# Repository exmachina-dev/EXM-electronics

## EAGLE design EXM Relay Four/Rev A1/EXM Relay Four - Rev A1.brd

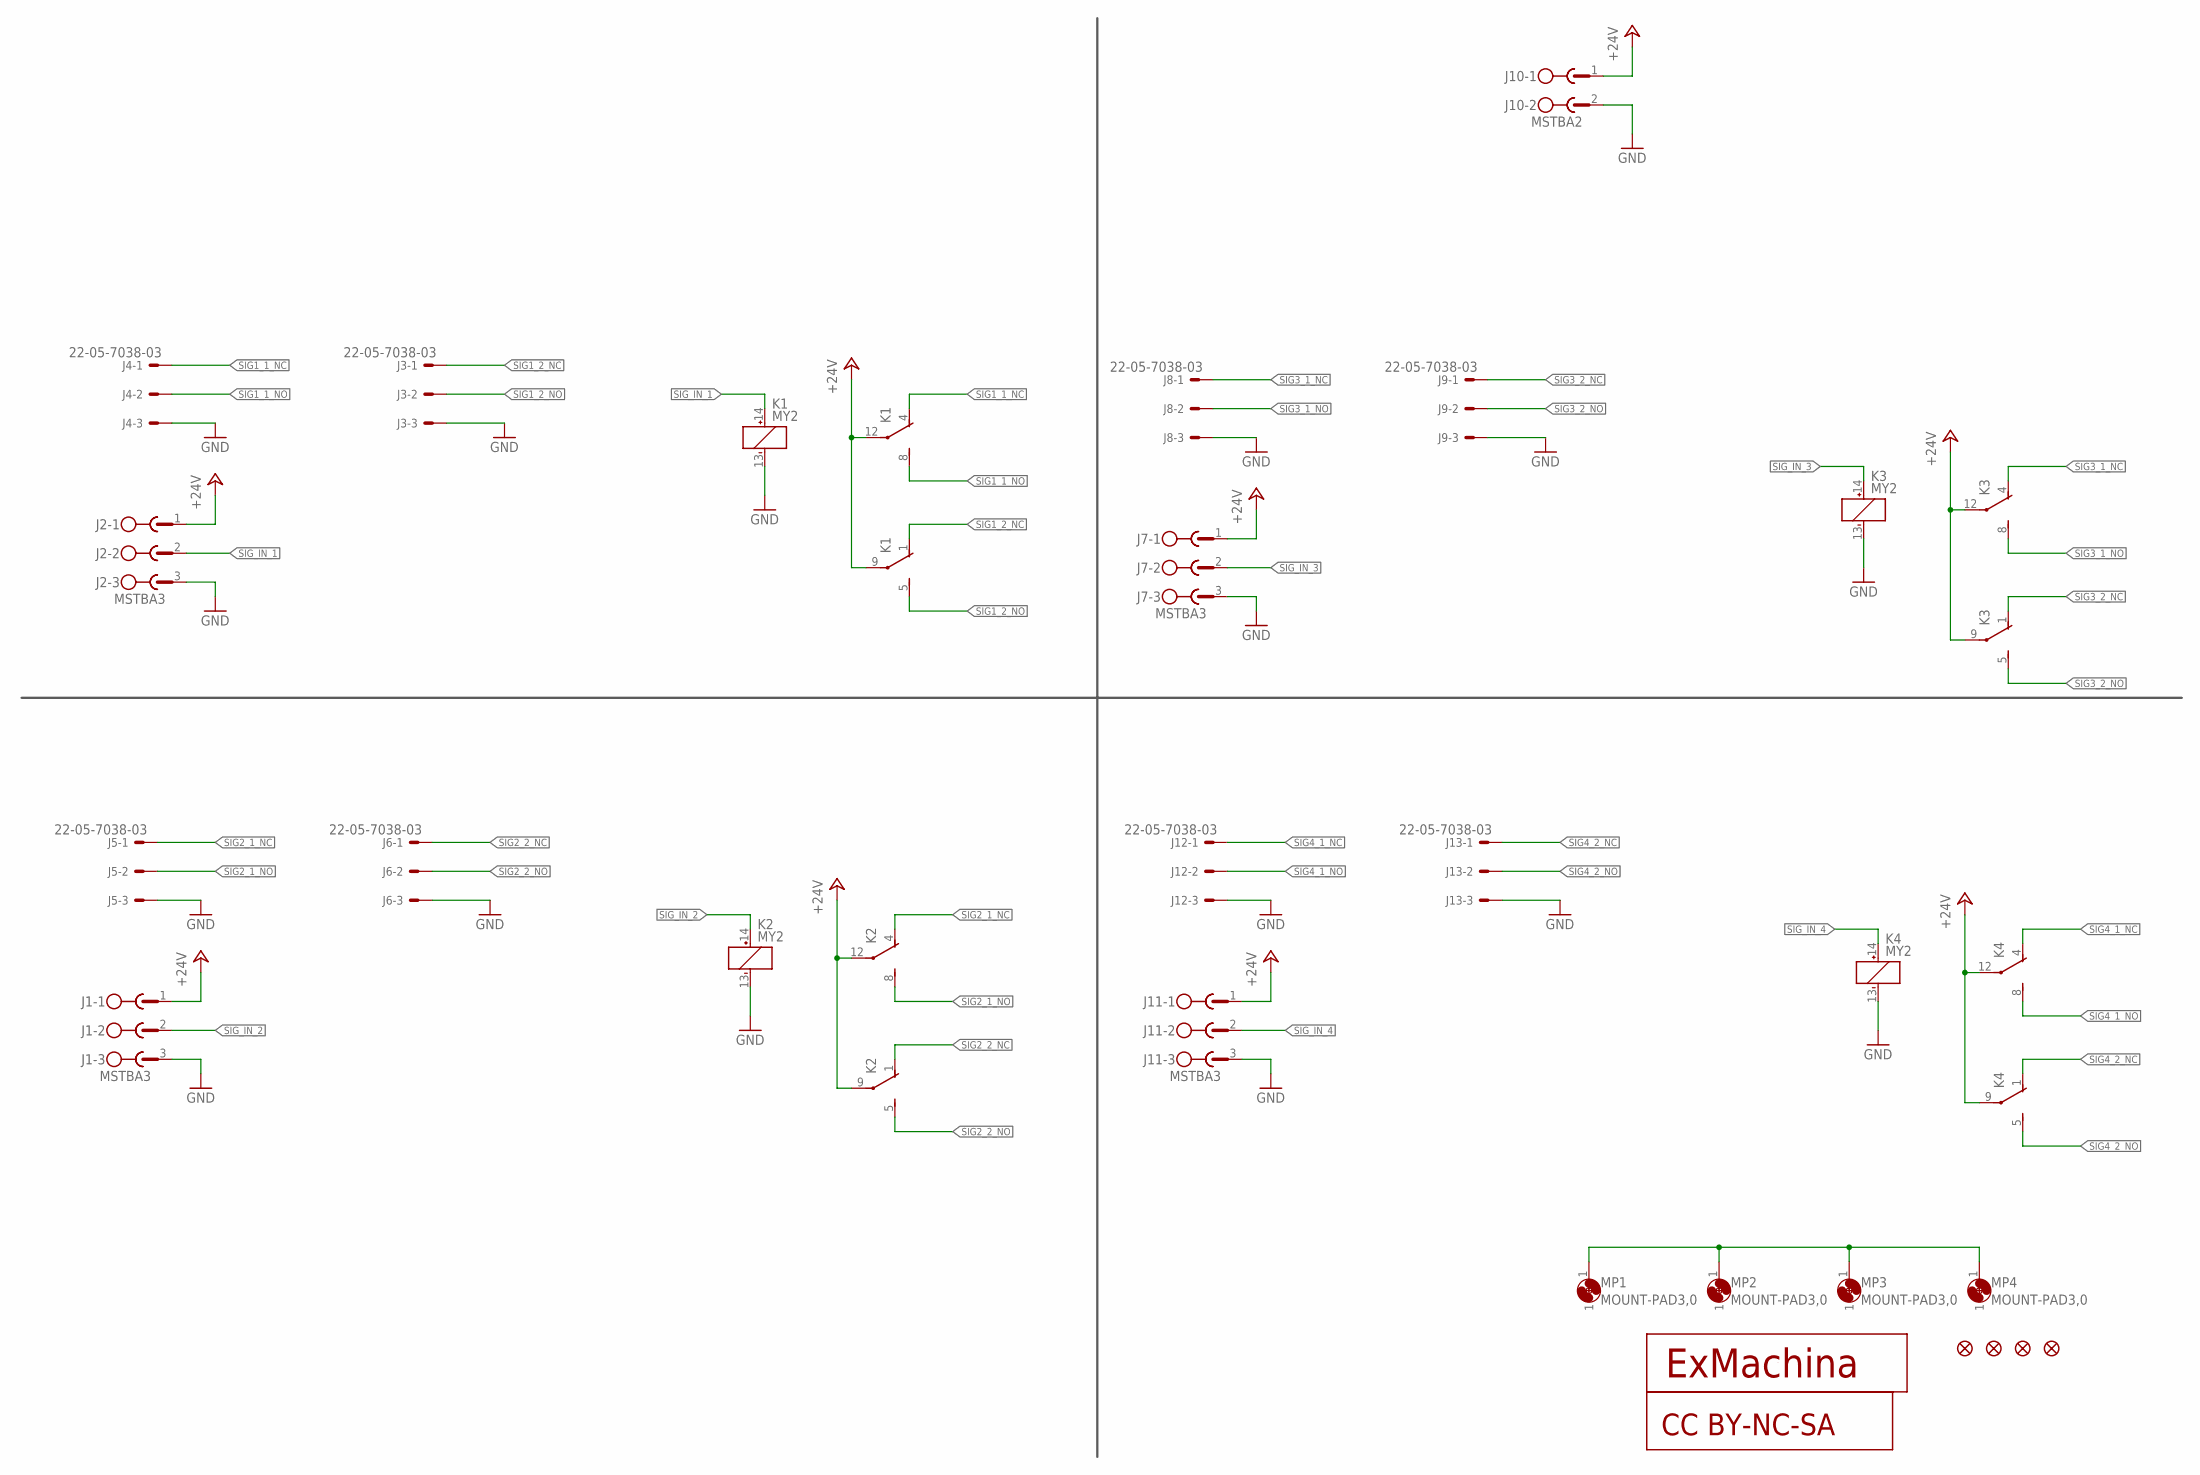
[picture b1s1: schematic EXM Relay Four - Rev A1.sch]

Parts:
CC1: CC-BY-NC-SA
J1, J2, J7, J11: MSTBA3
J3, J4, J5, J6, J8, J9, J12, J13: 22-05-7038-03; 7395-03
J10: MSTBA2
JP1, JP2, JP3, JP4: FIDUCIAL1X2; FIDUCIAL-1X2
K1, K2, K3, K4: MY2; PY08
MP1, MP2, MP3, MP4: MOUNT-PAD3,0; P3,0
T1: EXMACHINA-LOGO-NAME; EXM-LOGO-BASELINE

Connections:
1: MP1.1, MP2.1, MP3.1, MP4.1
+24V: J1.1, J2.1, J7.1, J10.1, J11.1, K1.9 (C), K1.12 (C), K2.9 (C), K2.12 (C), K3.9 (C), K3.12 (C), K4.9 (C), K4.12 (C)
GND: J1.3, J2.3, J3.3, J4.3, J5.3, J6.3, J7.3, J8.3, J9.3, J10.2, J11.3, J12.3, J13.3, K1.13 (-), K2.13 (-), K3.13 (-), K4.13 (-)
SIG1_1_NC: J4.1, K1.4 (NC)
SIG1_1_NO: J4.2, K1.8 (NO)
SIG1_2_NC: J3.1, K1.1 (NC)
SIG1_2_NO: J3.2, K1.5 (NO)
SIG2_1_NC: J5.1, K2.4 (NC)
SIG2_1_NO: J5.2, K2.8 (NO)
SIG2_2_NC: J6.1, K2.1 (NC)
SIG2_2_NO: J6.2, K2.5 (NO)
SIG3_1_NC: J8.1, K3.4 (NC)
SIG3_1_NO: J8.2, K3.8 (NO)
SIG3_2_NC: J9.1, K3.1 (NC)
SIG3_2_NO: J9.2, K3.5 (NO)
SIG4_1_NC: J12.1, K4.4 (NC)
SIG4_1_NO: J12.2, K4.8 (NO)
SIG4_2_NC: J13.1, K4.1 (NC)
SIG4_2_NO: J13.2, K4.5 (NO)
SIG_IN_1: J2.2, K1.14 (+)
SIG_IN_2: J1.2, K2.14 (+)
SIG_IN_3: J7.2, K3.14 (+)
SIG_IN_4: J11.2, K4.14 (+)

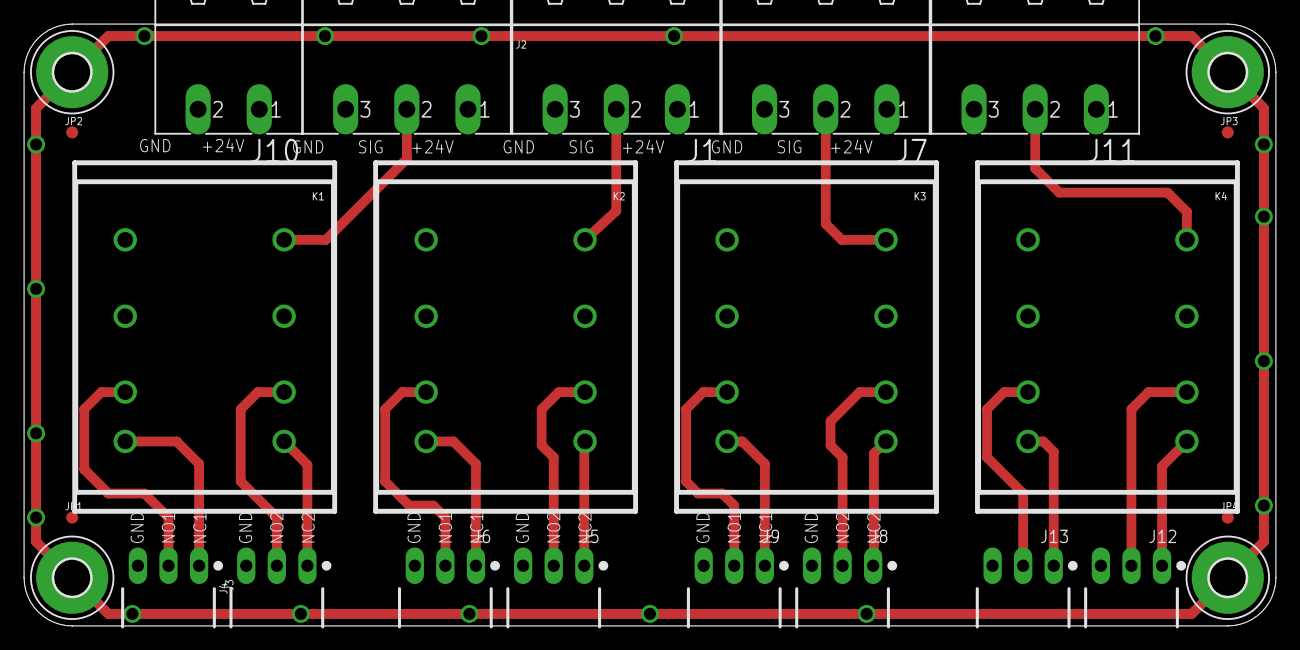
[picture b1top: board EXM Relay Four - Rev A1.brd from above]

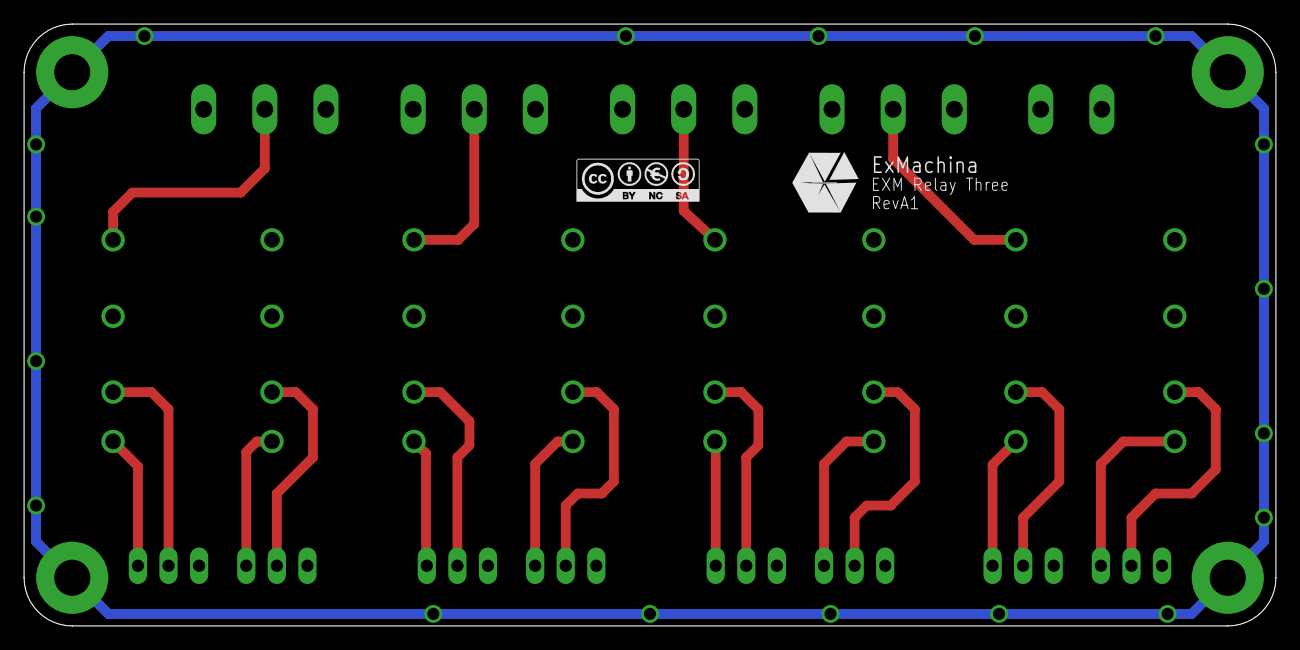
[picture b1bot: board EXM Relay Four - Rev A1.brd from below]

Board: 2 copper layers, 104.0 x 50.0 mm, 28 parts (2 on the bottom side), 23 nets.

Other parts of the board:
U$1: A4L-LOC

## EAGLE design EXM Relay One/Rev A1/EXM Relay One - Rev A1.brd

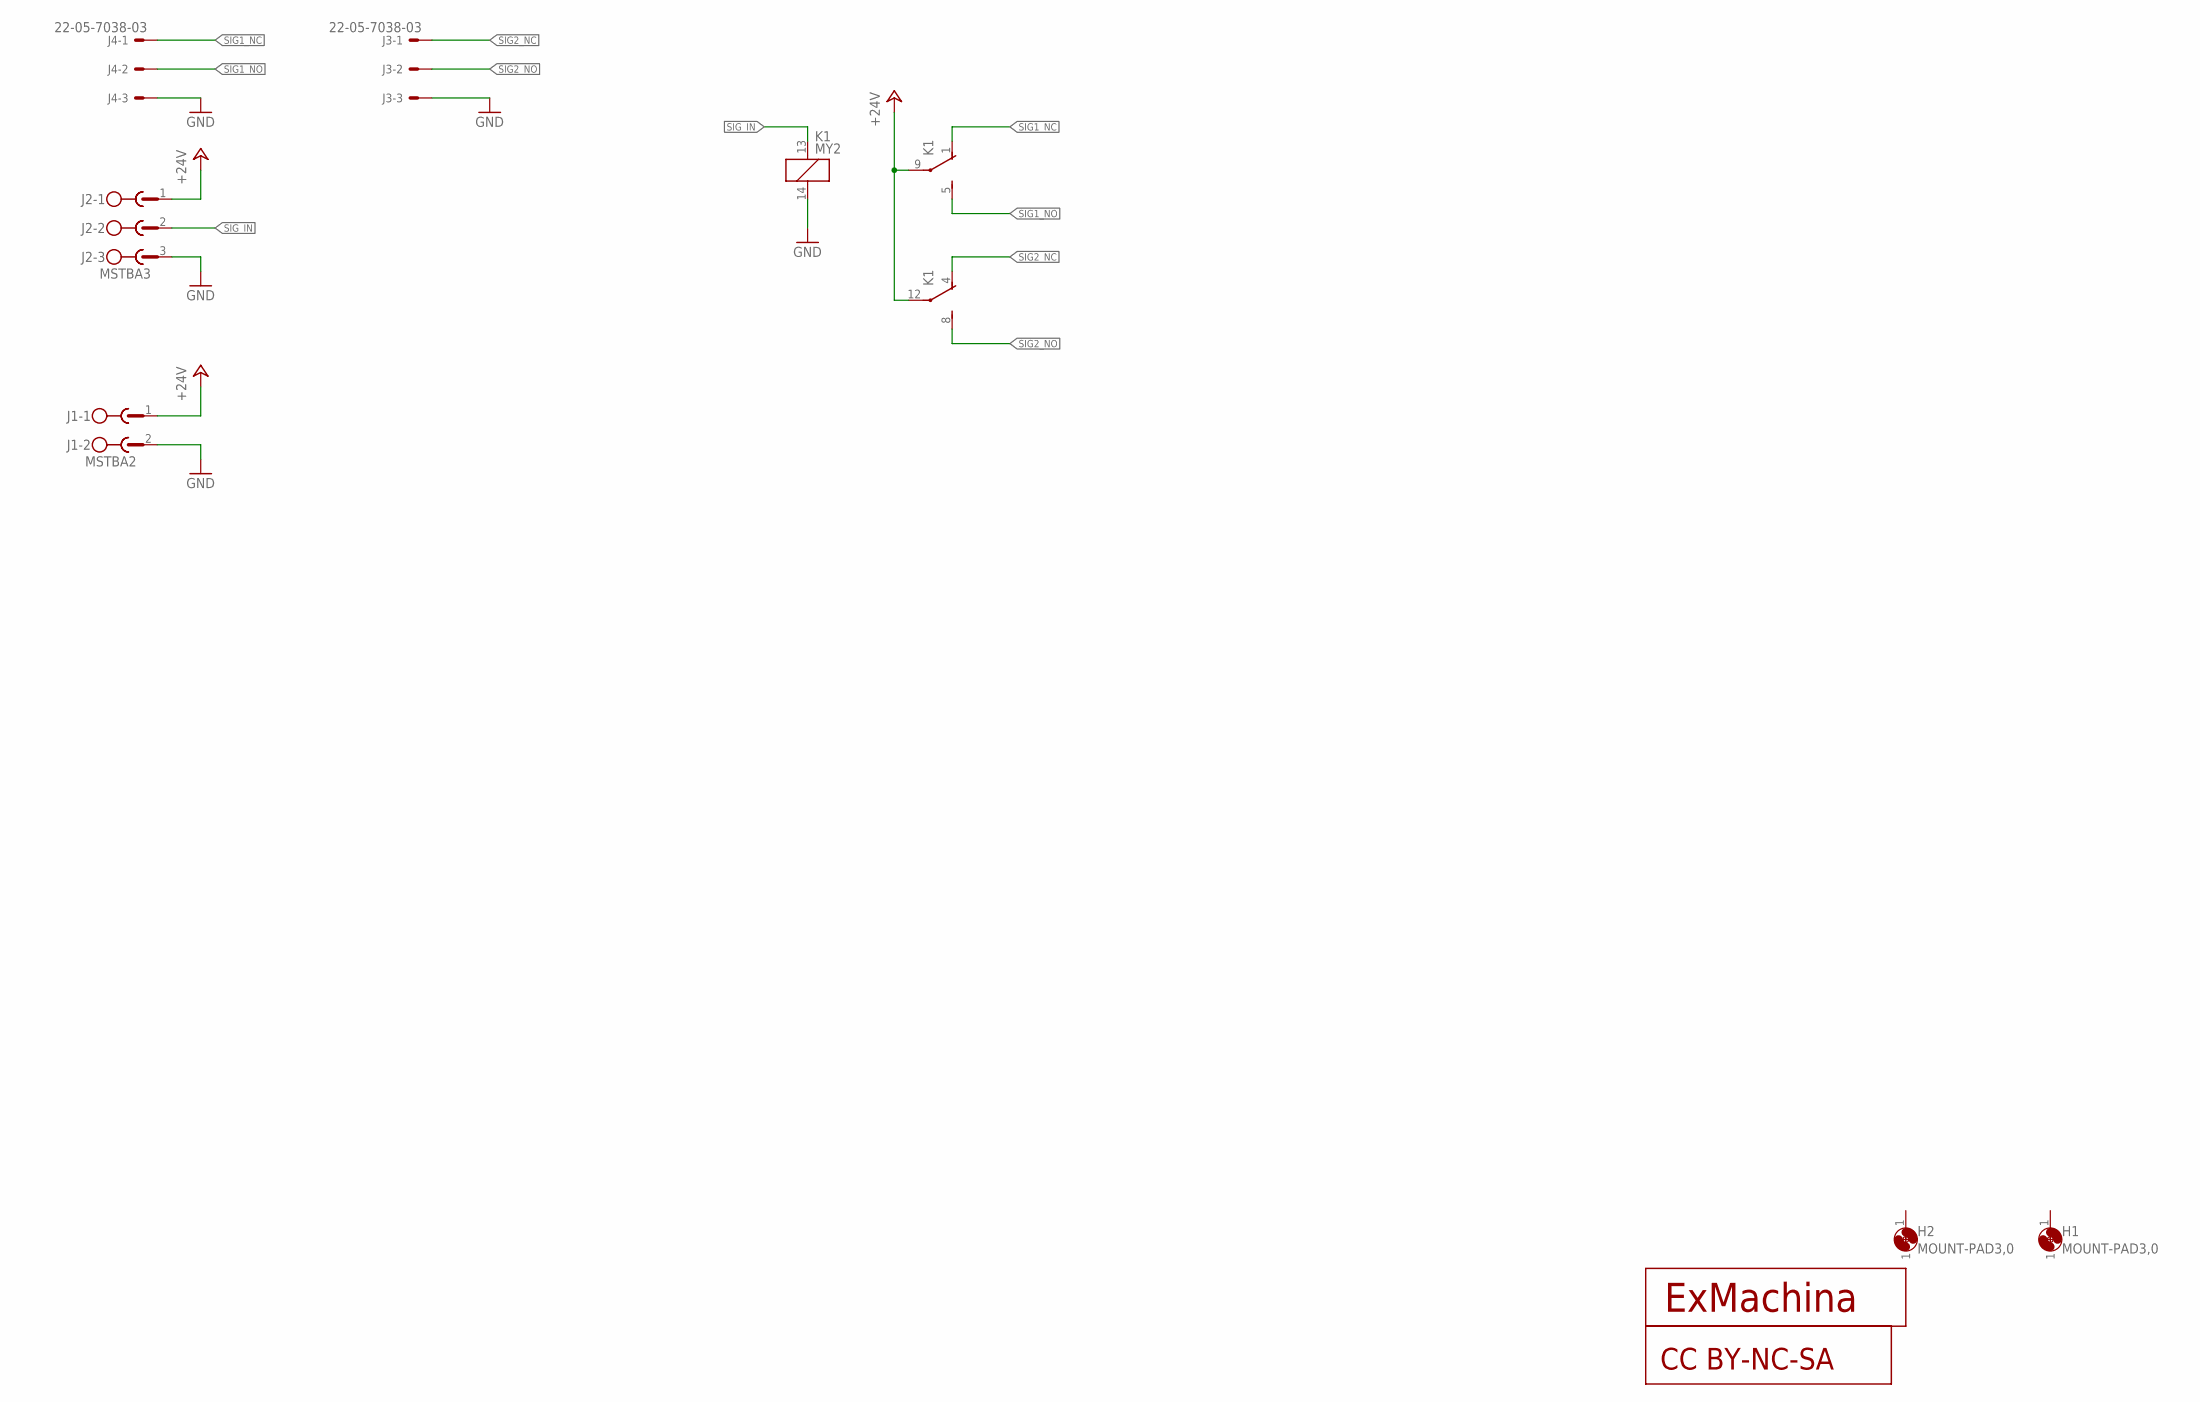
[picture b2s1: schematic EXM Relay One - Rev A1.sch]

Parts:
CC1: CC-BY-NC-SA
H1, H2: MOUNT-PAD3,0; P3,0
J1: MSTBA2
J2: MSTBA3
J3, J4: 22-05-7038-03; 7395-03
K1: MY2; PY08
T1: EXMACHINA-LOGO-NAME; EXM-LOGO-BASELINE

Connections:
+24V: J1.1, J2.1, K1.9 (C), K1.12 (C)
GND: J1.2, J2.3, J3.3, J4.3, K1.14 (COIL2)
SIG1_NC: J4.1, K1.1 (NO)
SIG1_NO: J4.2, K1.5 (NC)
SIG2_NC: J3.1, K1.4 (NO)
SIG2_NO: J3.2, K1.8 (NC)
SIG_IN: J2.2, K1.13 (COIL1)

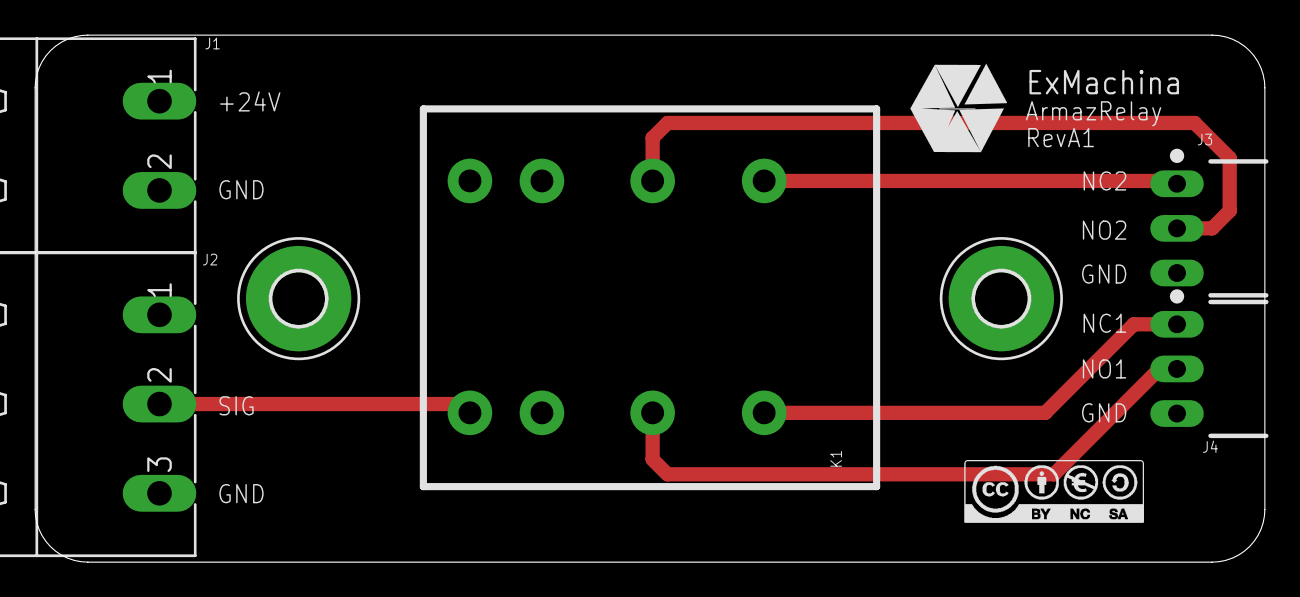
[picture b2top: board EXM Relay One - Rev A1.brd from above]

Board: 2 copper layers, 70.0 x 30.0 mm, 10 parts (0 on the bottom side), 7 nets.

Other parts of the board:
U$1: A4L-LOC

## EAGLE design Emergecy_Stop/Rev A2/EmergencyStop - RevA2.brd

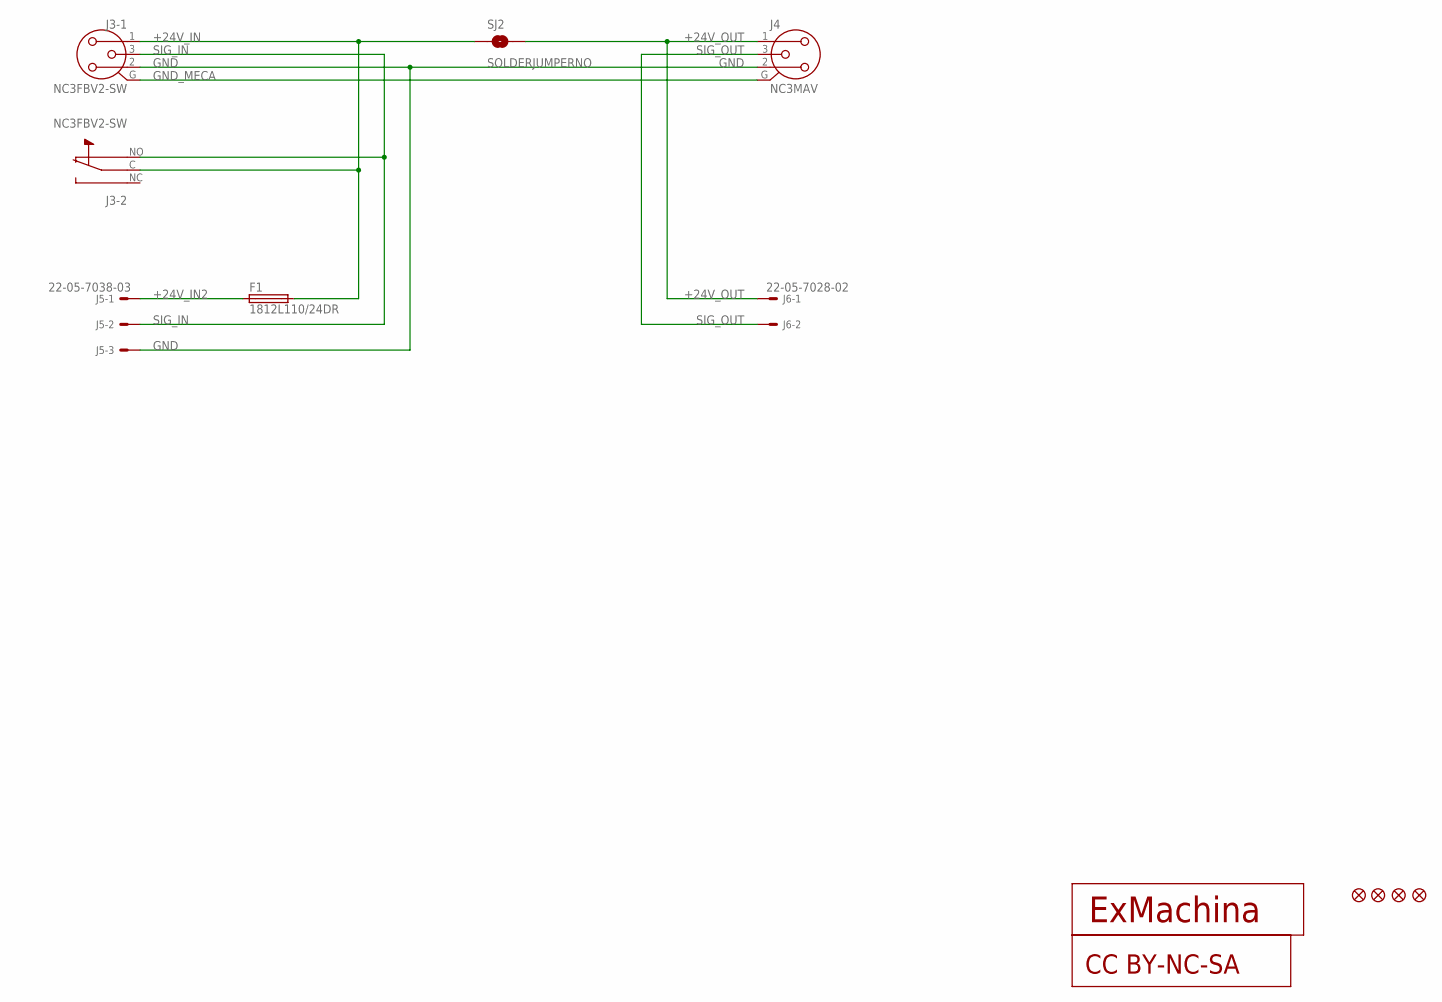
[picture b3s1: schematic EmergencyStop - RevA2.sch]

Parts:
CC1: CC-BY-NC-SA
F1: 1812L110/24DR; LITTLEFUSE_SMD
J3: NC3FBV2-SW
J4: NC3MAV
J5: 22-05-7038-03; 7395-03
J6: 22-05-7028-02; 7395-02
JP1, JP2, JP3, JP4: FIDUCIAL1X2; FIDUCIAL-1X2
SJ2: SOLDERJUMPERNO; SJ_2S-NO
T1: EXMACHINA-LOGO-NAME; EXM-LOGO-BASELINE

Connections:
+24V_IN: F1.2, J3.1, J3.C (N), SJ2.1
+24V_IN2: F1.1, J5.1
+24V_OUT: J4.1, J6.1, SJ2.2
GND: J3.2, J4.2, J5.3
GND_MECA: J3.G, J4.G
SIG_IN: J3.3, J3.NO, J5.2
SIG_OUT: J4.3, J6.2

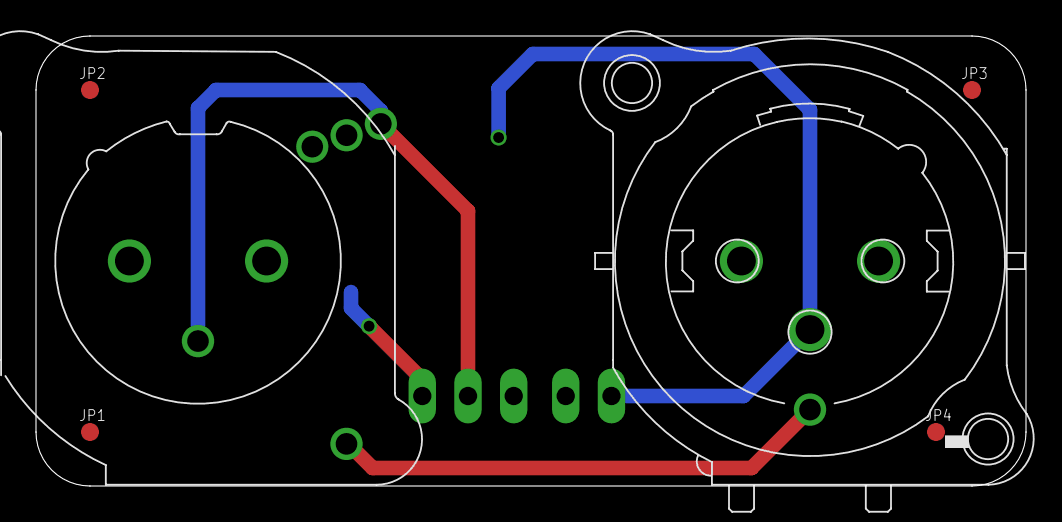
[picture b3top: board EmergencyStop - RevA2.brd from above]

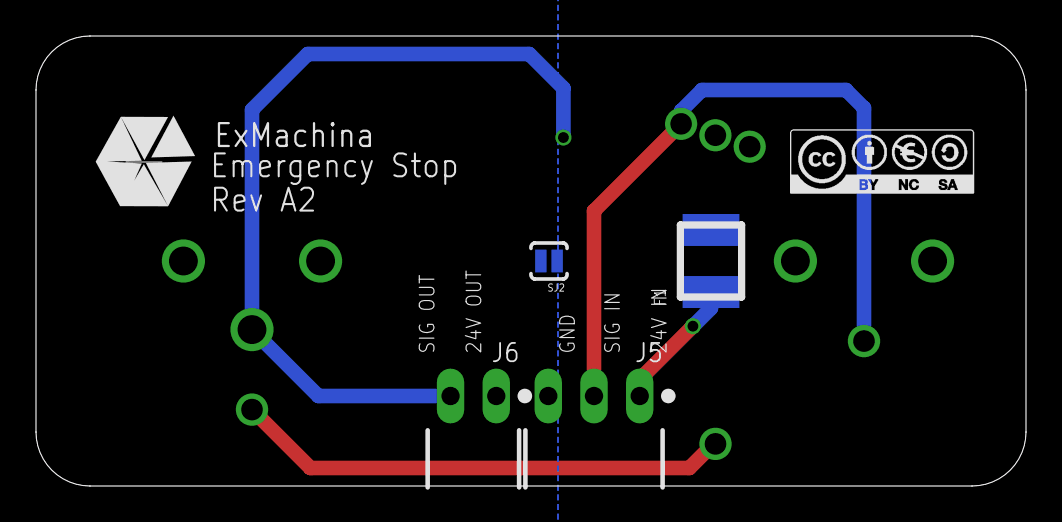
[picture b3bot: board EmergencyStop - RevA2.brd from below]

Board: 2 copper layers, 55.0 x 25.0 mm, 12 parts (6 on the bottom side), 7 nets.

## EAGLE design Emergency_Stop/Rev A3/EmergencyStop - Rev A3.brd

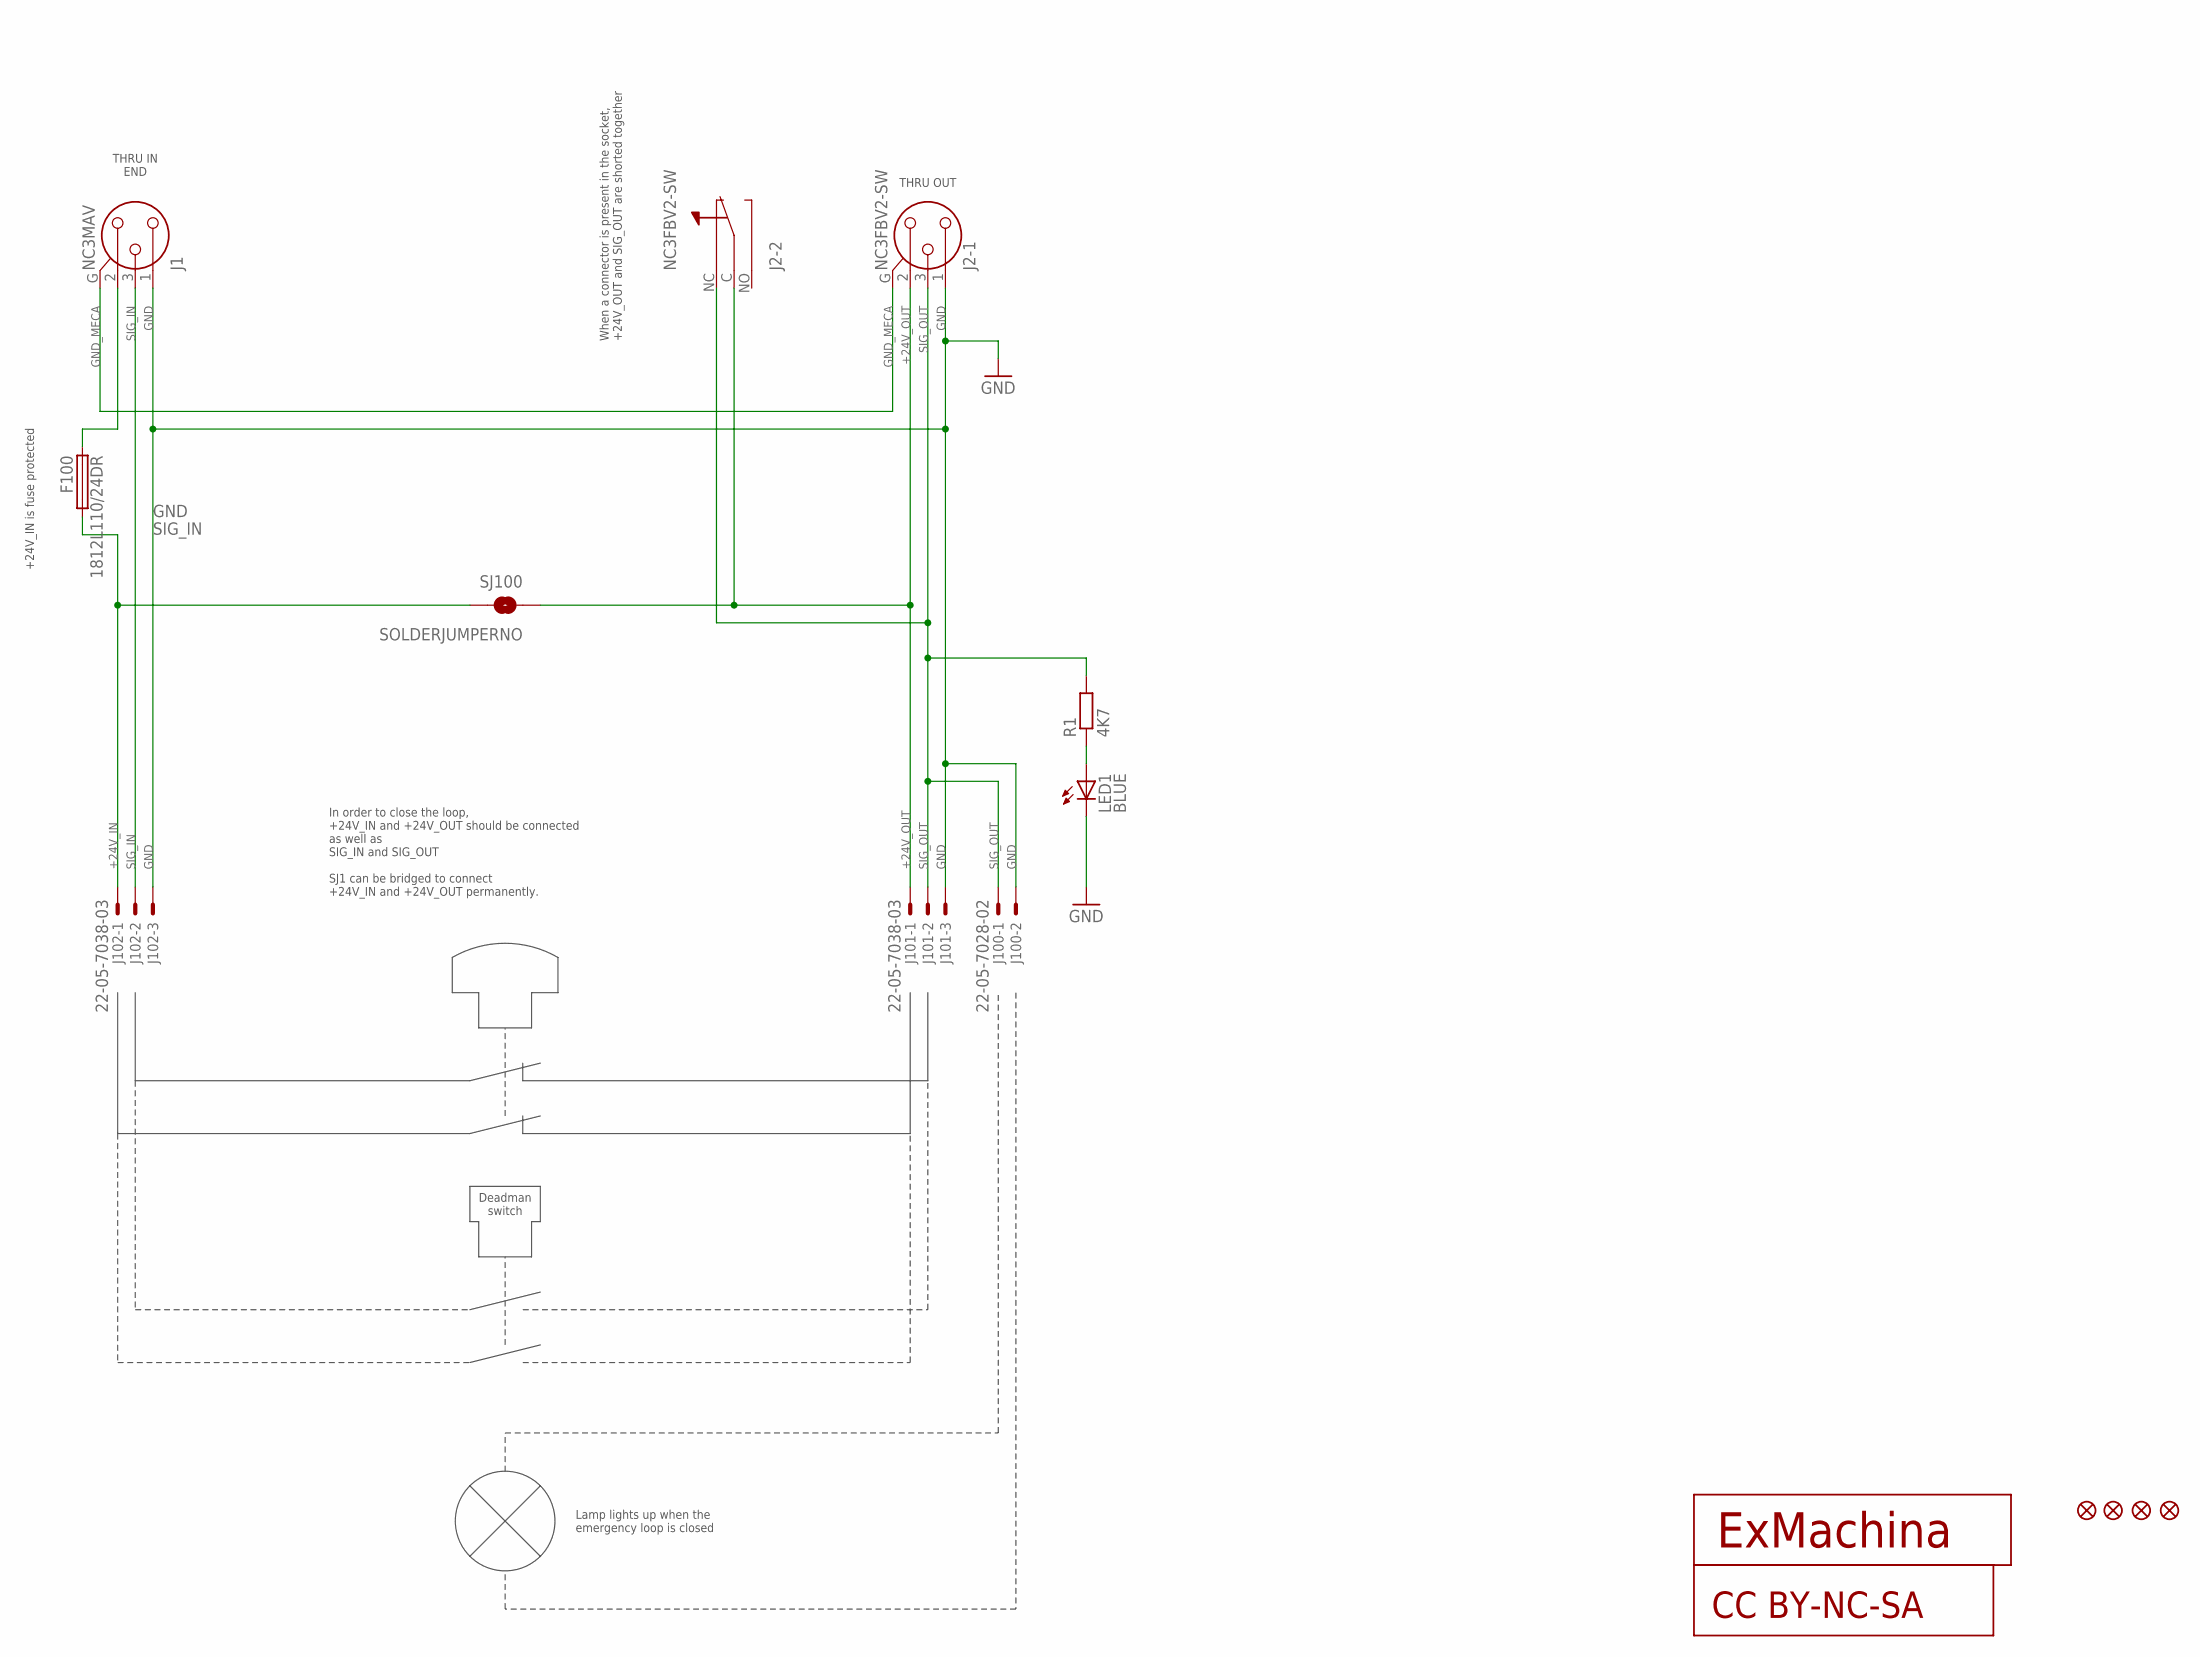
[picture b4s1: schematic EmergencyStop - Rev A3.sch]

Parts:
CC100: CC-BY-NC-SA
F100: 1812L110/24DR; LITTLEFUSE_SMD; MPN 1812L110/24DR
J1: NC3MAV
J2: NC3FBV2-SW
J100: 22-05-7028-02; 7395-02
J101, J102: 22-05-7038-03; 7395-03
JP100, JP101, JP102, JP103: FIDUCIAL1X2; FIDUCIAL-1X2
LED1: BLUE; CHIPLED_0603; MPN OVS-0603
R1: 4K7; R0603; MPN RC0603FR-074K7L
SJ100: SOLDERJUMPERNO; SJ_2S-NO
T100: EXMACHINA-LOGO-NAME; EXM-LOGO-BASELINE

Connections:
+24V_IN: F100.2, J102.1, SJ100.2
+24V_OUT: J2.2, J2.C (N), J101.1, SJ100.1
GND: J1.1, J2.1, J100.2, J101.3, J102.3, LED1.C
GND_MECA: J1.G, J2.G
unnamed: F100.1, J1.2
unnamed: LED1.A, R1.1
SIG_IN: J1.3, J102.2
SIG_OUT: J2.3, J2.NC, J100.1, J101.2, R1.2

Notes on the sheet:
Deadman switch
Lamp lights up when the emergency loop is closed
In order to close the loop, +24V_IN and +24V_OUT should be connected as well as SIG_IN and SIG_OUT SJ1 can be bridged to connect +24V_IN and +24V_OUT permanently.
+24V_IN is fuse protected
When a connector is present in the socket, +24V_OUT and SIG_OUT are shorted together
THRU IN END
THRU OUT

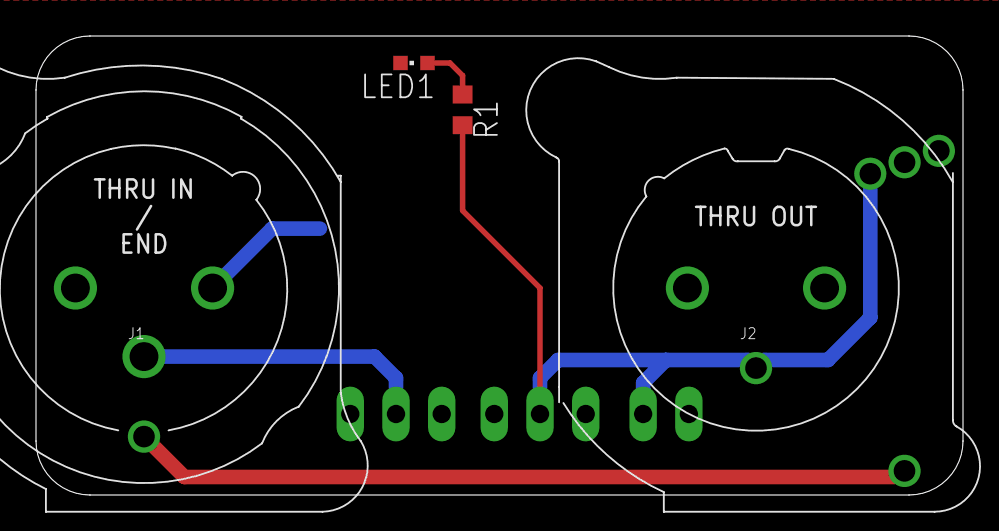
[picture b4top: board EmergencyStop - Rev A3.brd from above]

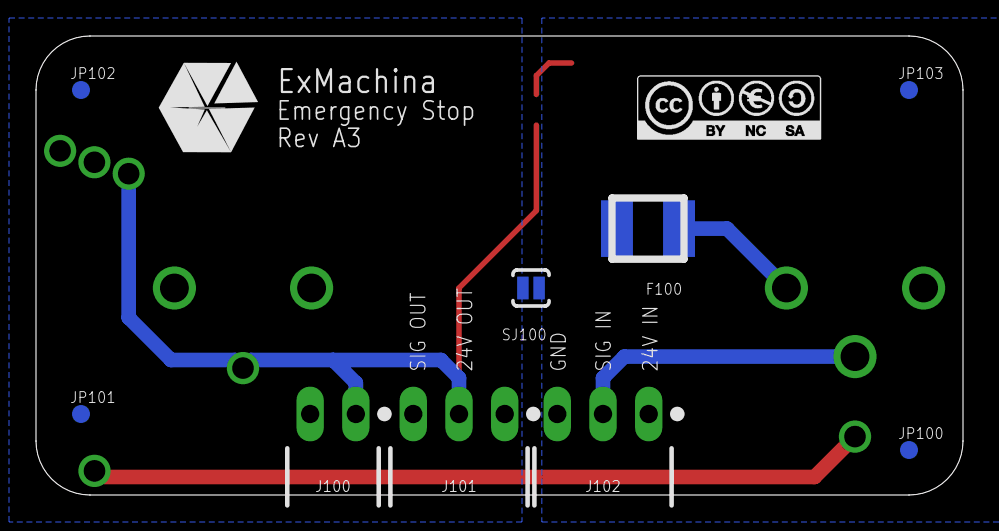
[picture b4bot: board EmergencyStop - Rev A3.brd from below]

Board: 2 copper layers, 51.5 x 25.5 mm, 16 parts (11 on the bottom side), 8 nets.

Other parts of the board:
U$1: A4L-LOC
